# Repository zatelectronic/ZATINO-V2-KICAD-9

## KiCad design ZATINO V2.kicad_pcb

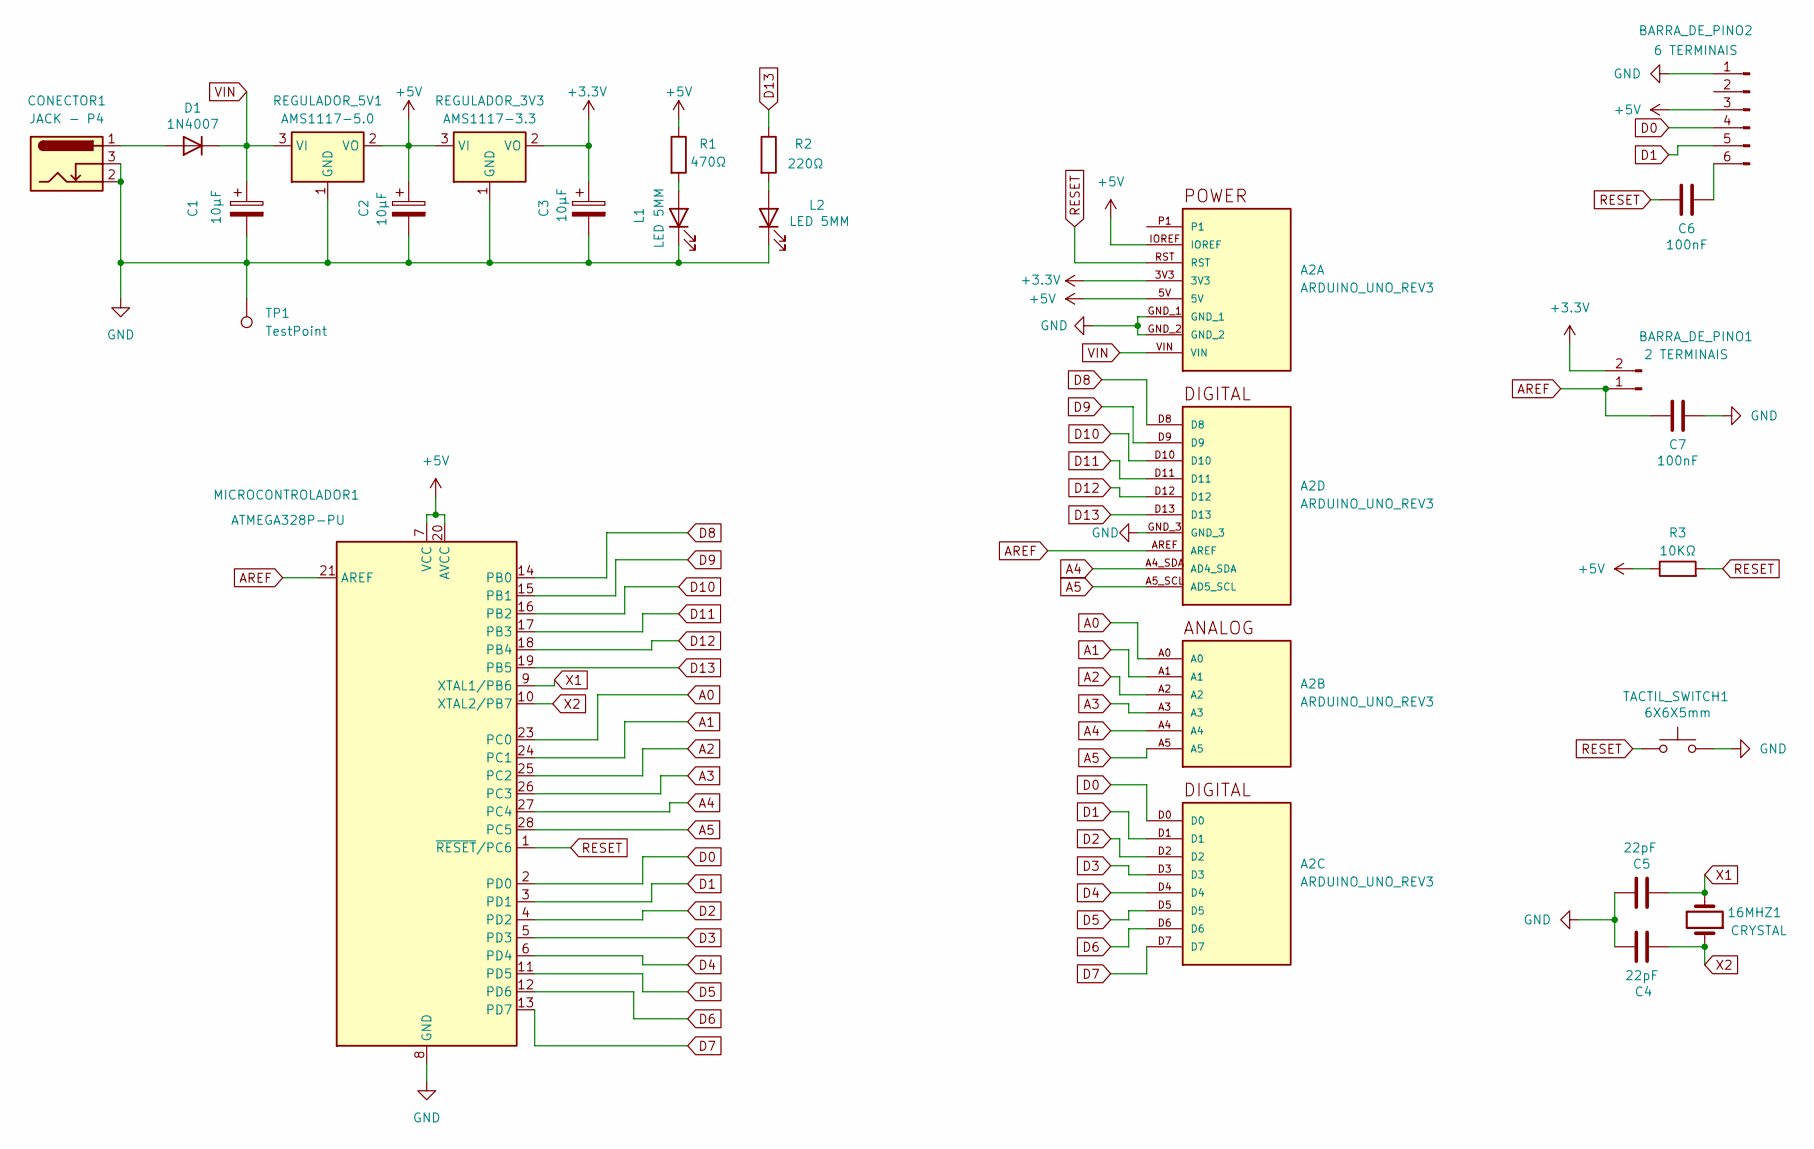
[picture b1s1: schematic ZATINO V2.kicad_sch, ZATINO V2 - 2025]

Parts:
16MHZ1: CRYSTAL; Crystal_HC18-U_Vertical
A2: ARDUINO_UNO_REV3; ARDUINO_ARDUINO_UNO_REV3; PARTREV N/A
BARRA_DE_PINO1: 2 TERMINAIS; PinHeader_1x02_P2.54mm_Vertical
BARRA_DE_PINO2: 6 TERMINAIS; PinHeader_1x06_P2.54mm_Vertical
C1, C2, C3: 10μF; CP_Radial_D5.0mm_P2.50mm
C4, C5: 22pF; C_Disc_D3.0mm_W1.6mm_P2.50mm
C6, C7: 100nF; C_Disc_D3.0mm_W2.0mm_P2.50mm
CONECTOR1: JACK - P4; BarrelJack_Horizontal
D1: 1N4007; D_DO-41_SOD81_P10.16mm_Horizontal
L1, L2: LED 5MM; LED_D5.0mm
MICROCONTROLADOR1: ATMEGA328P-PU; DIP-28_W7.62mm
R1: 470Ω; R_Axial_DIN0204_L3.6mm_D1.6mm_P7.62mm_Horizontal
R2: 220Ω; R_Axial_DIN0204_L3.6mm_D1.6mm_P7.62mm_Horizontal
R3: 10KΩ; R_Axial_DIN0204_L3.6mm_D1.6mm_P7.62mm_Horizontal
REGULADOR_3V3: AMS1117-3.3; SOT-223-3_TabPin2
REGULADOR_5V1: AMS1117-5.0; SOT-223-3_TabPin2
TACTIL_SWITCH1: 6X6X5mm; SW_PUSH_6mm_H5mm
TP1: TestPoint; TestPoint_Pad_3.0x3.0mm

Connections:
+3.3V: A2.3V3, BARRA_DE_PINO1.2, C3.1, REGULADOR_3V3.2 (VO)
+5V: A2.5V, A2.IOREF, BARRA_DE_PINO2.3, C2.1, MICROCONTROLADOR1.7 (VCC), MICROCONTROLADOR1.20 (AVCC), R1.1, R3.1, REGULADOR_3V3.3 (VI), REGULADOR_5V1.2 (VO)
A0: A2.A0, MICROCONTROLADOR1.23 (PC0)
A1: A2.A1, MICROCONTROLADOR1.24 (PC1)
A2: A2.A2, MICROCONTROLADOR1.25 (PC2)
A3: A2.A3, MICROCONTROLADOR1.26 (PC3)
A4: A2.A4, A2.A4_SDA (AD4_SDA), MICROCONTROLADOR1.27 (PC4)
A5: A2.A5, A2.A5_SCL (AD5_SCL), MICROCONTROLADOR1.28 (PC5)
AREF: A2.AREF, BARRA_DE_PINO1.1, C7.2, MICROCONTROLADOR1.21 (AREF)
D0: A2.D0, BARRA_DE_PINO2.4, MICROCONTROLADOR1.2 (PD0)
D1: A2.D1, BARRA_DE_PINO2.5, MICROCONTROLADOR1.3 (PD1)
D2: A2.D2, MICROCONTROLADOR1.4 (PD2)
D3: A2.D3, MICROCONTROLADOR1.5 (PD3)
D4: A2.D4, MICROCONTROLADOR1.6 (PD4)
D5: A2.D5, MICROCONTROLADOR1.11 (PD5)
D6: A2.D6, MICROCONTROLADOR1.12 (PD6)
D7: A2.D7, MICROCONTROLADOR1.13 (PD7)
D8: A2.D8, MICROCONTROLADOR1.14 (PB0)
D9: A2.D9, MICROCONTROLADOR1.15 (PB1)
D10: A2.D10, MICROCONTROLADOR1.16 (PB2)
D11: A2.D11, MICROCONTROLADOR1.17 (PB3)
D12: A2.D12, MICROCONTROLADOR1.18 (PB4)
D13: A2.D13, MICROCONTROLADOR1.19 (PB5), R2.1
GND: A2.GND_1, A2.GND_2, A2.GND_3, BARRA_DE_PINO2.1, C1.2, C2.2, C3.2, C4.2, C5.2, C7.1, CONECTOR1.2, CONECTOR1.3, L1.1 (K), L2.1 (K), MICROCONTROLADOR1.8 (GND), MICROCONTROLADOR1.22 (GND), REGULADOR_3V3.1 (GND), REGULADOR_5V1.1 (GND), TACTIL_SWITCH1.2, TP1.1
unnamed: BARRA_DE_PINO2.6, C6.1
unnamed: CONECTOR1.1, D1.2 (A)
unnamed: L1.2 (A), R1.2
unnamed: L2.2 (A), R2.2
RESET: A2.RST, C6.2, MICROCONTROLADOR1.1 (~RESET/PC6), R3.2, TACTIL_SWITCH1.1
VIN: A2.VIN, C1.1, D1.1 (K), REGULADOR_5V1.3 (VI)
X1: 16MHZ1.2, C5.1, MICROCONTROLADOR1.9 (XTAL1/PB6)
X2: 16MHZ1.1, C4.1, MICROCONTROLADOR1.10 (XTAL2/PB7)

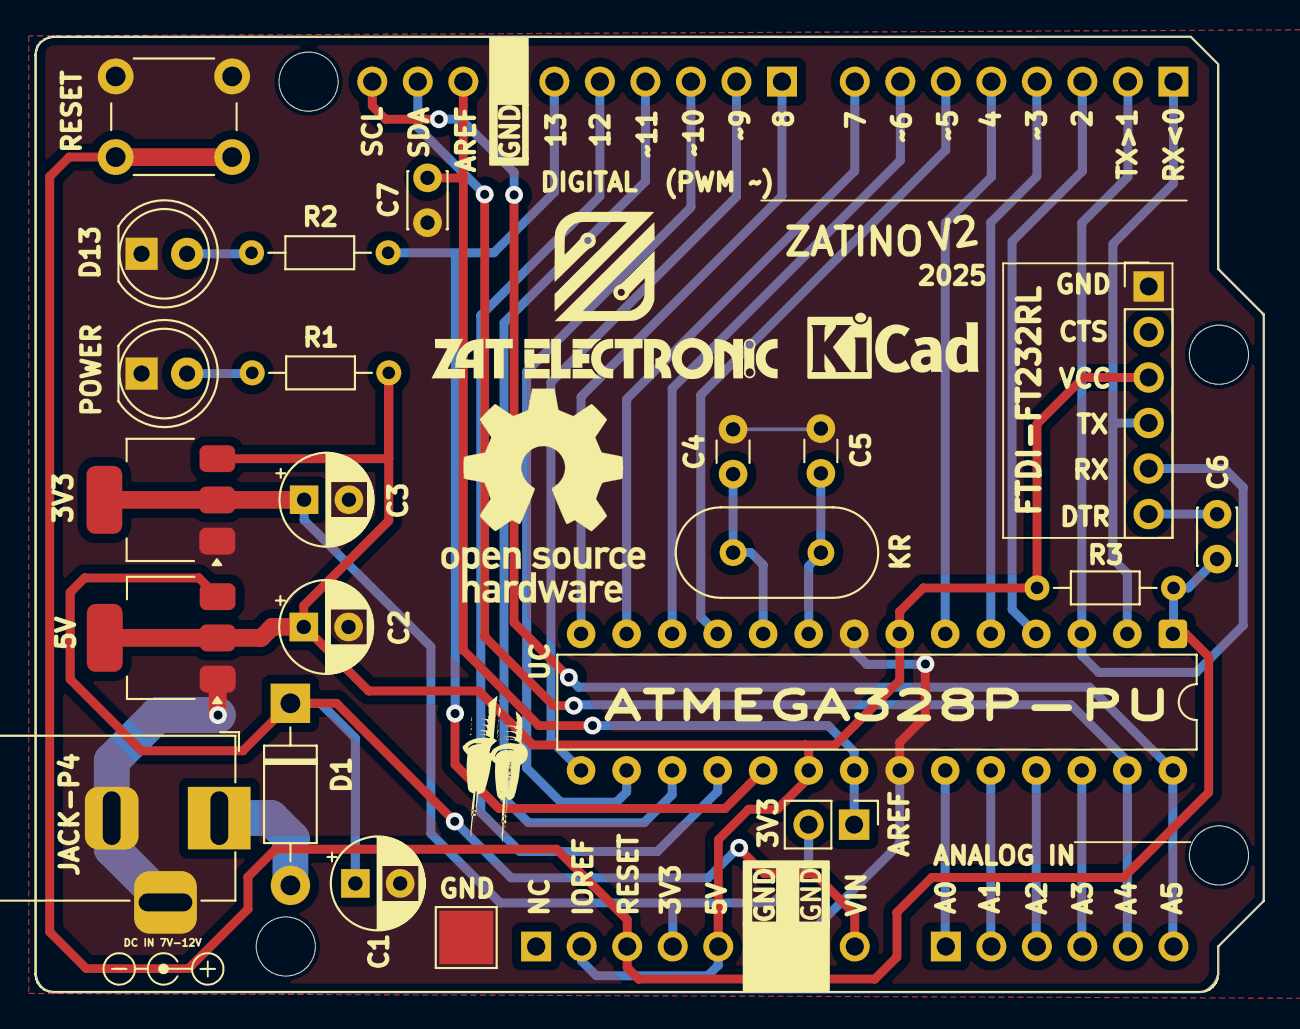
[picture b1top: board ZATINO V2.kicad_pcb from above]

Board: 2 copper layers, 68.5 x 53.4 mm, 23 parts (0 on the bottom side), 32 nets.
